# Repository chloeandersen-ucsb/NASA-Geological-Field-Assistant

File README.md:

# **S**urface **A**ssistant for **G**eological **E**valuation 
A field system for real-time lunar rock classification. Runs on a NVIDIA Jetson Orin NX with a microphone, camera, and LED display. A ground UI on a separate machine lets Earth-based mission control review collected data.

## system overview

Camera captures an image of a rock, RockNet classifies it, and the volume estimator measures its dimensions. All information is shown on LED display in real time. Meanwhile the MEMS mic streams to the voice transcriber, which appends timestamped field notes. 

Everything gets written to `sage_store/` on the Jetson. After a session, `scripts/transfer_to_ground.ps1` pulls that folder to the ground machine, where `ground-UI` lets mission control browse the full mission log.

### where data lives

| Data | File(s) | Notes |
|---|---|---|
| Captured images | `ML-classifications/camera-pipeline/images/YYYYMMDD/*.jpg` | one folder per day |
| Rock classification | `*_prediction.json` + `sage_store/rocks.jsonl` | prediction.json stays with image; jsonl is the running log |
| Volume + mass | `*_volume.json` | merged into the rock's entry in `rocks.jsonl` |
| Voice notes | `sage_store/voice_notes.jsonl` | timestamped transcripts, keyed to rock sample |
| Mission index | `sage_store/missions.json` | groups rocks into named missions |

## quick start

```bash
make setup      # install dependencies + download models
make check      # verify setup
make run        # production mode (full pipeline)
make run-mock   # mock data (no hardware needed)
make run-mock-ml  # real voice transcription, mock ML
```

## display controls

| Key | Action |
|---|---|
| Joystick / arrow keys | navigate rocks |
| ESC | exit fullscreen |
| CTRL+C | quit |
| Quit button | quit |

## folders

| Folder | What it does |
|---|---|
| [`ML-classifications/`](ML-classifications/) | rock classifier |
| [`led-display/`](led-display/) | PySide6 UI |
| [`voiceNotes/`](voiceNotes/) | live speech-to-text for field annotations |
| [`rock-volume/`](rock-volume/) | volume + mass calculations |
| [`ground-UI/`](ground-UI/) | browser-based mission review application |
| [`pcb/`](pcb/) | MEMS microphone breakout board (KiCad) |
| [`microphone-testing/`](microphone-testing/) | audio test samples |
| [`scripts/`](scripts/) | data transfer utilities |

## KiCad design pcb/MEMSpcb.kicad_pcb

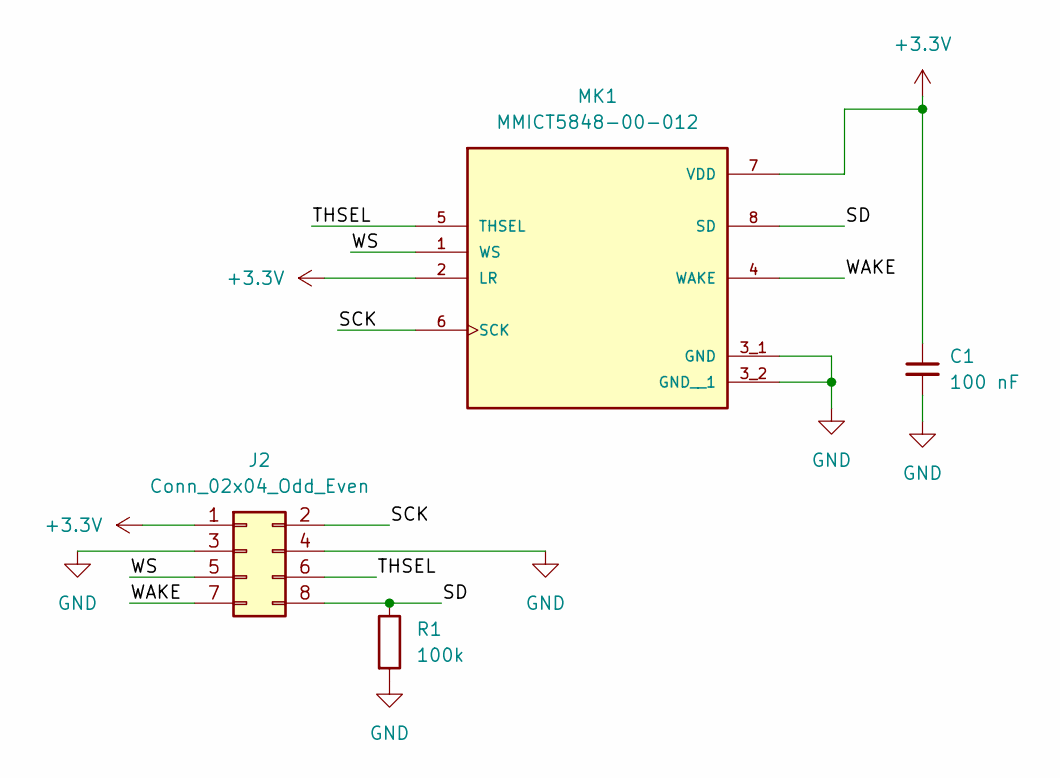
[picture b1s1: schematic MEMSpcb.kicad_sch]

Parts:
C1: 100 nF; CP_EIA-3528-12_Kemet-T_Pad1.50x2.35mm_HandSolder; LCSC C122257
J2: Conn_02x04_Odd_Even; PinHeader_2x04_P2.00mm_Vertical
MK1: MMICT5848-00-012; MIC_MMICT5848-00-012; PARTREV 1.0; LCSC C20344623
R1: 100k; R_01005_0402Metric_Pad0.57x0.30mm_HandSolder; LCSC C270298

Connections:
+3.3V: C1.1, J2.1, MK1.2 (LR), MK1.7 (VDD)
/SCK: J2.2, MK1.6 (SCK)
/SD: J2.8, MK1.8 (SD), R1.1
/THSEL: J2.6, MK1.5 (THSEL)
/WAKE: J2.7, MK1.4 (WAKE)
/WS: J2.5, MK1.1 (WS)
GND: C1.2, J2.3, J2.4, MK1.3_1 (GND), MK1.3_2 (GND__1), R1.2

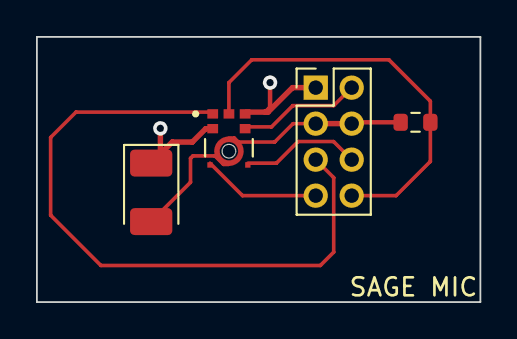
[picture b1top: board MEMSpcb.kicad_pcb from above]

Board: 4 copper layers, 24.6 x 14.7 mm, 4 parts (0 on the bottom side), 7 nets.

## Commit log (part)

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2025-11-07 Add full 3D reconstruction pipeline + UI
2025-11-13 on-device inference script for rock ml classification
2025-11-13 Add files via upload
    This is the currently working version for voice transcription on the Orin.
2025-11-15 readme updates
2025-11-15 updating file path
2025-11-15 Revise configuration instructions in README.md
    Updated paths and configuration instructions in README.
2025-11-27 MEMS pcb
2025-11-27 moving into folder
2025-12-03 fixed routing sizes, pad error, and resistor error
2025-12-03 fixed routing sizes, pad error and resistor error
2025-12-04 Update 3d-reconstructions with new pipeline code
2025-12-04 updated transcription files
2025-12-05 added bom and stuff
2026-01-09 final transcript cleaned up
2026-01-23 checking old audio file
2026-01-23 trying to figure out mic device number
2026-01-23 last mic devices
2026-01-23 last hope for pcb
2026-01-23 testing lav mic
2026-01-23 routing to correct device
2026-01-23 checking changes in sr
2026-01-23 first rendition of stt program on jetson w lav mic
2026-01-23 demo for meeting
2026-01-23 organizing file structure
2026-01-23 deleting copy
2026-01-26 Create temp.txt
    Just to create a folder
2026-01-26 Added newest transcription script
2026-01-27 Rename improved2-2.py to transcriber_fine_tuned.py
2026-01-27 Rename geology_model2-2-2.nemo to newest_model.nemo
2026-01-27 Rename improved2.py to original_model.py
2026-01-27 Rename score3.py to score.py
    This script assigns a model a score based on ground truth and received output
2026-01-27 Add .gitignore file for Python project
2026-01-27 Update Makefile
2026-01-28 adding debugging statements
2026-01-28 adding exit commands
2026-01-28 adding debugging for voice to text displaying on led, also adding flush to improved2.py
2026-01-28 adding a loading page and some logic for duplications
2026-01-28 cleaning up a bit and adding some ui features
2026-01-28 removing comments + cleaning up
2026-01-29 copy of functioning rtt
2026-01-29 still picking up silence
2026-01-30 clean up
2026-01-30 trying to patch up mismatch issues
2026-01-30 fixing tracebacks (cpu/gpu issues)
2026-01-30 threshold testing
2026-01-30 normalization testing
2026-01-30 fixing up final transcript
2026-01-30 final transcript fixing
2026-01-30 last resort for final transcript
2026-01-30 decoder failing for final transcript
2026-01-30 cleaning up final transcript
2026-01-30 final cleaned up final transcript
2026-01-30 making new voice to text compatible
2026-02-02 Merged multimodal logic with robust audio buffering
2026-02-02 Fixed errord in merged file
2026-02-03 Added smart grammar and tried adding punctuation
2026-02-06 modified files for pcb
2026-02-06 camera pipeline + integrating real ML with led
2026-02-06 showing all 3 classification options
2026-02-06 only showing other classification scores if > 0% confidence
2026-02-10 adding camera pipeline + optimizing codebase
2026-02-11 updating requirements to redownload on jetson & be compatible
2026-02-11 logs for testing
2026-02-11 more testing
2026-02-11 final debug + removing logs
2026-02-11 removing unnecessary stuff
2026-02-11 checking feature
2026-02-11 fixing voice to text and camera bugs
2026-02-11 Revert "only showing other classification scores if > 0% confidence"
    This reverts commit 7c62837c02cb67df5d5a8776663432f9fc611a21.
2026-02-12 playing around with ui
2026-02-12 testing ui
2026-02-12 trying to reformat home screen
2026-02-12 issues with displaying image
2026-02-12 image loaded, playing with colors
2026-02-12 colors + bg
2026-02-12 fonts
2026-02-12 font change working
2026-02-12 playing with font case
2026-02-12 playing with font and style
2026-02-12 trying to edit voice notes page
2026-02-12 voice notes page edited
2026-02-13 home screen and stt ui cleaned up
2026-02-15 configuring voice to text to ilai model, not shruthi. to still be tested
2026-02-16 adding camera pipeline
2026-02-17 pushing ilai's changes (just one file)
2026-02-18 save button bug fixed + ui complete
2026-02-18 ui bug with transcription fixed
2026-02-18 Optimize startup and fix LFS tracking for large nemo file
2026-02-19 Add startup latency timer to fine-tuned transcriber
2026-02-19 Now the vtt model loads before the GUI appears. Next goal will be to not completely kill the transcriber when stopping the recording
2026-02-20 Now only need to load the model oncegit add .
2026-02-23 Completed camera pipeline, still need to do tests with actual display
2026-02-26 UI: finalized seamless image scaling and fixed window resizing
2026-02-27 first rendition of vtt in classify, still needs work
2026-02-28 Add rock-analysis module with timestamp-based output filenames
2026-02-28 Remove 3d-reconstructions folder
2026-03-03 Streamline rock measurement pipeline: consolidate to single measure_rock.py entry point, remove obsolete modes and redundant code, update SETUP.md
2026-03-03 Add outputs directories to gitignore
2026-03-04 rock volume integration
2026-03-04 adding .nemo to gitignore
2026-03-04 stopping tracking nemo file so .gitignore ignores it in the future
2026-03-05 sequentially running classification then volume to try to save GPU
2026-03-05 some ui fixes and adding volume logging
2026-03-05 making sure error messages arent on app window, and fixing total weight calculation in tripnotes
2026-03-05 adding some error handling - error button to analyzing page, preventing infinite loops, proper cleanup
2026-03-05 adding .nemo file back, with Git LFS to store large files
2026-03-05 Added keyboard (still not 100%)
2026-03-05 fitting fullscreen on every page
2026-03-05 next screen size fitting test
2026-03-05 changing location of where voice notes save to inside codebase - should probably change this later
2026-03-05 making sure voice notes json are in gitignore
2026-03-05 initial apriltag detection logic
2026-03-06 ui cleaned up
2026-04-01 trying to fix (more broken than main currently
2026-04-08 stt fix complete! needs to be merged into main
2026-04-09 going back to pre merge
2026-04-09 spacing
2026-04-09 fixes from merge + bugs found by claude code
2026-04-09 fixing small bug + exiting boot model upon failure instead of infinite loop
2026-04-09 lowercase to fix bug of not opening on jetson
2026-04-09 Fixed merge issues and organized buttons in VTT
2026-04-11 Fix Windows mock startup and transcription boot hangs
2026-04-14 just some file reorg
2026-04-15 Added Create New Mission button to TripLoadPage
2026-04-16 Add PowerShell pull script for Jetson output transfer
2026-04-16 transfer script standardized for other networks/devices, still requires same network
2026-04-17 remove temperature argument
2026-04-17 cuda bug fixes
2026-04-20 Code only - absolutely no models
2026-04-20 Fixed AI Summarizer & made a small change in VTT
2026-04-23 Changed text into a HTML table and ignored models folder
2026-04-23 Reinforce model ignoring
2026-04-28 Improved VTT
2026-04-29 My next changes change the way final transcript works - it might not re-listen to everything anymore
2026-04-29 Auto capitalization and punctutation
2026-04-30 base version, still needs to be cleaned up
2026-04-30 Fix transcriber unterminated string literal and update core services
2026-05-05 Switched to a different model
2026-05-05 Added loading screen
2026-05-05 Fixed problem where it would duplicate last word
2026-05-05 pre-updated model version
2026-05-05 Fixed AI Summarizer
2026-05-05 joystick debug
2026-05-05 updating trip notes page for joystick
2026-05-05 more tripnotes debugging
2026-05-05 trip notes fixing ux
2026-05-05 changing initial button highlight
2026-05-06 ui changes start
2026-05-06 updating gitignore
2026-05-06 Finalized AI Summarizer
2026-05-06 Edited home screen
2026-05-07 fix joystick logic and add gitignore
2026-05-07 new logo + gitignore
2026-05-07 Restoring to just ML changes - no UI changes yet
2026-05-07 updating gitignore and connecting new model to rest of program without ui changes
2026-05-07 Revert "Merge pull request #9 from chloeandersen-ucsb/general-ml"
    This reverts commit 2b1bf8640baa673d482b49a404839431538918e6, reversing
    changes made to 239fb4f4f69c1844c0e396f10934a134af8d62d1.
    reverting back to ilai's commit (pre updated ML model)
2026-05-07 updating gitignore and removing untrack dev/device-only files
2026-05-07 updating gitignore to align with main + removing untracked dev/device only files
2026-05-07 removing files that are now untracked and should be on device only
2026-05-07 connector updates
2026-05-07 compatibility with new ml model
2026-05-08 fullscreen fix
2026-05-08 removing ilai pictures lol
2026-05-08 gitignore
2026-05-08 fixing navbar
2026-05-08 fixing navbar and keeping background transparent
2026-05-08 updated rock classification design?
2026-05-08 some classified page updates:
2026-05-08 more ui updates :
2026-05-08 fixing spacing
2026-05-08 feature table fit
2026-05-08 final quick updates
2026-05-13 Fixed problems with empty recording and joystick not locking on 'Stop' button during VTT
2026-05-17 adding setup script. deleting unused files. updating makefile
2026-05-18 Update transfer branch with ground UI
2026-05-19 improving ml readme + adding classification results to trip notes
2026-05-19 device specific rotation
2026-05-19 debug
2026-05-19 last debug?
2026-05-19 few updates:
2026-05-19 small adjustments
2026-05-19 fixing inconsistencies
2026-05-19 adding border radius to images
2026-05-19 more adjustments
2026-05-19 going back
2026-05-19 reducing length of geology notes
2026-05-19 geology notes page in classified page
2026-05-19 trying to streamline buttons
2026-05-19 mission button
2026-05-19 one more color change
2026-05-19 cleanup
2026-05-19 more button stuff:
2026-05-19 restoring geology notes for clearness of PR
2026-05-19 oops
2026-05-19 one more
2026-05-20 Added loading screen & realized battery might be a bit more complicated than I thought
2026-05-20 Fixed VTT bugs
2026-05-20 making readme for all sections
2026-05-20 trip notes joystick fix
2026-05-21 Fix parser image indexing collision bug and regenerate missions with 19 samples
    - Changed get_image_files() to key images by filename instead of timestamp
    to prevent overwrite collisions when multiple JPGs share same second
    - Updated images_by_filename comprehension to work with new keying
    - Parser now preserves all 75 images; mission 20260517_185713 now has 19 samples
    instead of 15 due to recovered collided files
    - Regenerated missions.json with complete sample set
2026-05-21 removing QMessageBox - not compatible with joystick
2026-05-21 load ML classification model once, rather than each time
2026-05-21 more efficiency + better logs
2026-05-21 removing logs: :
2026-05-21 cancel during classification bug
2026-05-21 time import
2026-05-21 reverting apriltag changes
2026-05-21 alternative classification button options
2026-05-21 final bugs
2026-05-21 adding confidence value to alt classification
2026-05-21 fixing text bug
2026-05-21 initial save bug
2026-05-21 streamlining joystick highlight color - to still be tested
2026-05-21 final joystick cleanups
2026-05-22 Battery percentage can be changed
2026-05-25 Add ML models via LFS
2026-05-26 Fine tuned again
2026-05-26 Done editing file (for now)
2026-05-26 volume apriltag hotfix
2026-05-27 adding battery state to gitignore
2026-05-27 adding logs to loading page
2026-05-27 Add AprilTag detection fallbacks
2026-05-27 simplify
2026-05-27 reverting vol changes
2026-05-27 text hotfix
2026-05-27 Added final model
2026-05-28 Now mission name can be recorded
2026-05-28 Added current mission to home page
2026-05-29 vtt parallel fixed
2026-05-30 Fixed some of the VTT issues
2026-05-30 More fixes
2026-05-31 adding cancel button to joystick
2026-06-02 some joystick things
2026-06-02 trip notes cancel button
2026-06-02 some debugs
2026-06-02 adding failsafe if we close app on joystick - 5 joystick button clicks to re open
2026-06-02 trip notes button cleanup
2026-06-02 adding some spacing
2026-06-02 fix: stale STREAMING COMPLETE wipes active session token buffer
2026-06-02 fix: _active flag dead code and _on_finished STREAMING COMPLETE handling
2026-06-02 debug: add finalization and routing debug logs
